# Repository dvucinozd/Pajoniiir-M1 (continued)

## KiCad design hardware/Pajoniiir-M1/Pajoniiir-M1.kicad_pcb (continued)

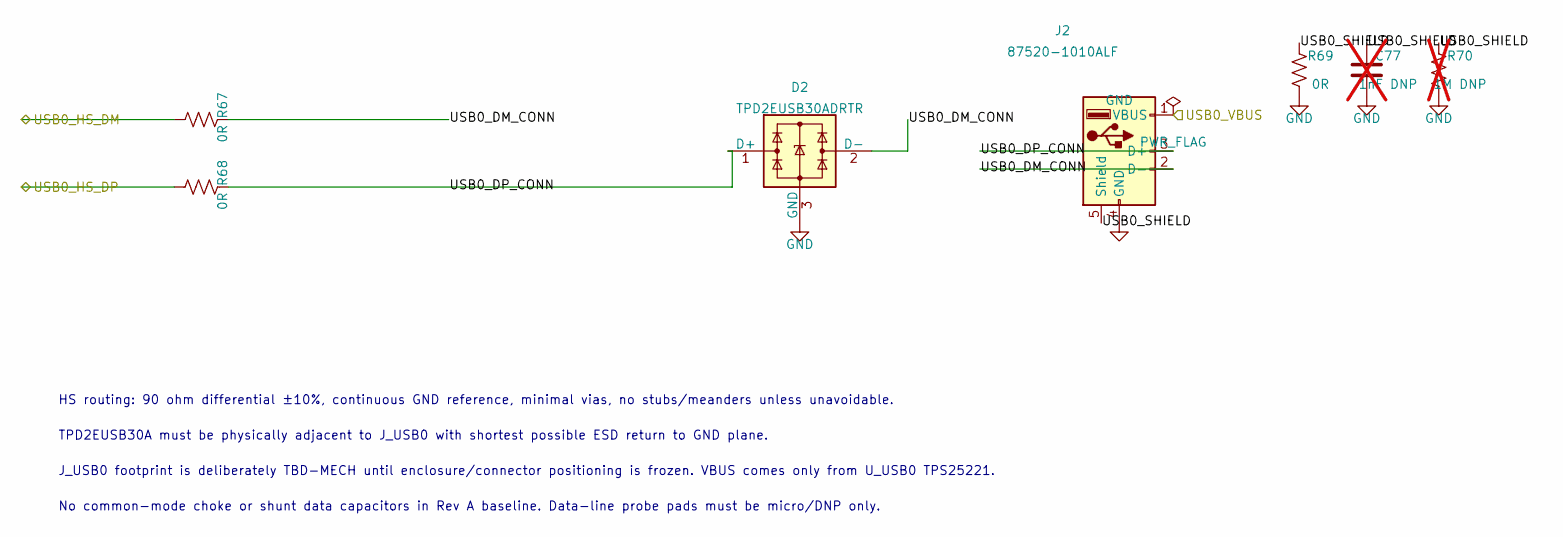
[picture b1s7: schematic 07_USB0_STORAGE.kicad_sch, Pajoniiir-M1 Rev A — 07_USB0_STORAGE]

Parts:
C77: 1nF DNP; C_0603_1608Metric; not fitted
D2: TPD2EUSB30ADRTR; Texas_DRT-3
J2: 87520-1010ALF; Amphenol_87520-1010ALF
R67, R68: 0R; R_0402_1005Metric
R69: 0R; R_0603_1608Metric
R70: 1M DNP; R_0603_1608Metric; not fitted

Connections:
/07_USB0_STORAGE/USB0_DM_CONN: D2.2 (D-), J2.2 (D-), R67.2
/07_USB0_STORAGE/USB0_DP_CONN: D2.1 (D+), J2.3 (D+), R68.2
/07_USB0_STORAGE/USB0_SHIELD: C77.1, J2.5 (Shield), R69.1, R70.1
/USB0_HS_DM: R67.1; also elsewhere on the board
/USB0_HS_DP: R68.1; also elsewhere on the board
/USB0_VBUS: J2.1 (VBUS); also elsewhere on the board

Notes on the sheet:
HS routing: 90 ohm differential ±10%, continuous GND reference, minimal vias, no stubs/meanders unless unavoidable.
TPD2EUSB30A must be physically adjacent to J_USB0 with shortest possible ESD return to GND plane.
J_USB0 footprint is deliberately TBD-MECH until enclosure/connector positioning is frozen. VBUS comes only from U_USB0 TPS25221.
No common-mode choke or shunt data capacitors in Rev A baseline. Data-line probe pads must be micro/DNP only.

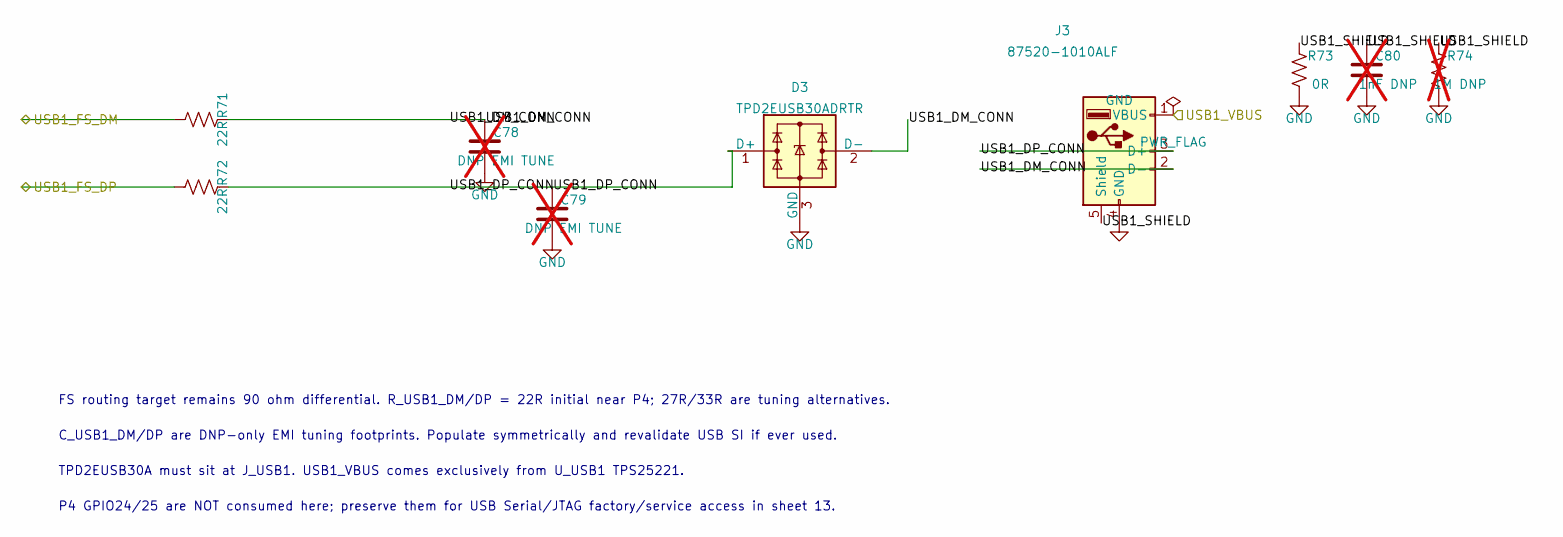
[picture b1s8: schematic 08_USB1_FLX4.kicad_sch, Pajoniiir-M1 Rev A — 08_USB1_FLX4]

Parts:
C78, C79: DNP EMI TUNE; C_0402_1005Metric; not fitted
C80: 1nF DNP; C_0603_1608Metric; not fitted
D3: TPD2EUSB30ADRTR; Texas_DRT-3
J3: 87520-1010ALF; Amphenol_87520-1010ALF
R71, R72: 22R; R_0402_1005Metric
R73: 0R; R_0603_1608Metric
R74: 1M DNP; R_0603_1608Metric; not fitted

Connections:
/08_USB1_FLX4/USB1_DM_CONN: C78.1, D3.2 (D-), J3.2 (D-), R71.2
/08_USB1_FLX4/USB1_DP_CONN: C79.1, D3.1 (D+), J3.3 (D+), R72.2
/08_USB1_FLX4/USB1_SHIELD: C80.1, J3.5 (Shield), R73.1, R74.1
/USB1_FS_DM: R71.1; also elsewhere on the board
/USB1_FS_DP: R72.1; also elsewhere on the board
/USB1_VBUS: J3.1 (VBUS); also elsewhere on the board

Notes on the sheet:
FS routing target remains 90 ohm differential. R_USB1_DM/DP = 22R initial near P4; 27R/33R are tuning alternatives.
C_USB1_DM/DP are DNP-only EMI tuning footprints. Populate symmetrically and revalidate USB SI if ever used.
TPD2EUSB30A must sit at J_USB1. USB1_VBUS comes exclusively from U_USB1 TPS25221.
P4 GPIO24/25 are NOT consumed here; preserve them for USB Serial/JTAG factory/service access in sheet 13.

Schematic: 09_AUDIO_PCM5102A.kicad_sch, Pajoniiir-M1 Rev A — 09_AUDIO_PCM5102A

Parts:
C81, C83, C85, C87: 10uF; C_0805_2012Metric
C82, C84, C86, C90: 100nF; C_0603_1608Metric
C88, C89: 2.2uF; C_0603_1608Metric
C91, C92: 2.2nF C0G; C_0603_1608Metric
J4: KLPX-0848A-2-W-G; Kycon_KLPX-0848A-2-x-G
J5: KLPX-0848A-2-R-G; Kycon_KLPX-0848A-2-x-G
R75, R76, R77: 22R; R_0402_1005Metric
R78: 100R; R_0603_1608Metric
R79: 100k; R_0603_1608Metric
R80, R81: 470R; R_0603_1608Metric
U5: PCM5102APWR; TSSOP-20_4.4x6.5mm_P0.65mm

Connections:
/3V3_AUDIO: C81.1, C82.1, C83.1, C84.1, C85.1, C86.1, C87.1, U5.1 (CPVDD), U5.8 (AVDD), U5.20 (DVDD); also elsewhere on the board
/09_AUDIO_PCM5102A/DAC_CAPM: C88.2, U5.4 (CAPM)
/09_AUDIO_PCM5102A/DAC_CAPP: C88.1, U5.2 (CAPP)
/09_AUDIO_PCM5102A/DAC_DATA_DAC: R76.2, U5.14 (DIN)
/09_AUDIO_PCM5102A/DAC_LDOO_1V8: C90.1, U5.18 (LDOO)
/09_AUDIO_PCM5102A/DAC_VNEG: C89.1, U5.5 (VNEG)
/09_AUDIO_PCM5102A/MAIN_L: C91.1, J4.1 (In), R80.2
/09_AUDIO_PCM5102A/MAIN_R: C92.1, J5.1 (In), R81.2
/DAC_BCLK: R77.1; also elsewhere on the board
/DAC_DATA: R76.1; also elsewhere on the board
/DAC_LRCK: R75.1; also elsewhere on the board
/DAC_XSMT: R78.1; also elsewhere on the board
unnamed: R77.2, U5.13 (BCK)
unnamed: R75.2, U5.15 (LRCK)
unnamed: R80.1, U5.6 (OUTL)
unnamed: R81.1, U5.7 (OUTR)
unnamed: R78.2, R79.1, U5.17 (XSMT)

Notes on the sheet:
PCM5102A 3-wire mode: SCK=GND; FMT=LOW (I2S); FLT=LOW; DEMP=LOW. No external MCLK is required.
XSMT defaults LOW via 100k pulldown. Firmware starts stable BCLK/LRCK/DATA, waits, then drives DAC_XSMT HIGH.
Single 3V3_AUDIO supply for CPVDD/DVDD/AVDD. LDOO is an internal ~1.8V output and is decoupled only.
MAIN_L/R are ground-centered DirectPath line outputs: 470R + 2.2nF, no series DC-block capacitors.
RCA J4/J5 Kycon KLPX-0848A gold-family footprints are locked; final panel XY/cutouts remain open. J6 / 3.5mm line-out was removed from Rev A in M1-MECH-A8; CUE/headphones remain via FLX4 USB Audio.

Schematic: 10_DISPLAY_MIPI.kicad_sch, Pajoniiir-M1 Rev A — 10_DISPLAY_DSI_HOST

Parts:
C93: 100nF; C_0603_1608Metric
C94: 10uF; C_0805_2012Metric
FB3: 0R / ferrite option; R_0603_1608Metric
J6: 15-pin Raspberry-Pi-style DSI host; Amphenol_SFW15R-2STE1LF
R82, R83, R84, R85, R86, R87: 0R; R_0201_0603Metric
R95, R96: 22R; R_0402_1005Metric
R97, R98: 4.7k; R_0603_1608Metric
R99, R100: 4.7k DNP; R_0603_1608Metric; not fitted
TP1: 3V3_DISPLAY_MODULE; TestPoint_Pad_D1.5mm
TP2: P4_LDO_MIPI_2V5; TestPoint_Pad_D1.5mm
TP9: J6_I2C_SDA; TestPoint_Pad_D1.5mm
TP10: J6_I2C_SCL; TestPoint_Pad_D1.5mm

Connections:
/3V3_SYS: FB3.1; also elsewhere on the board
/10_DISPLAY_MIPI/3V3_DISPLAY_MODULE: C93.1, C94.1, FB3.2, J6.14 (3V3), J6.15 (3V3), R97.1, R98.1, R99.1, R100.1, TP1.1
/10_DISPLAY_MIPI/J6_DSI_CLK_N: J6.5 (DSI_CLK_N), R87.2
/10_DISPLAY_MIPI/J6_DSI_CLK_P: J6.6 (DSI_CLK_P), R86.2
/10_DISPLAY_MIPI/J6_DSI_D0_N: J6.8 (DSI_D0_N), R83.2
/10_DISPLAY_MIPI/J6_DSI_D0_P: J6.9 (DSI_D0_P), R82.2
/10_DISPLAY_MIPI/J6_DSI_D1_N: J6.2 (DSI_D1_N), R85.2
/10_DISPLAY_MIPI/J6_DSI_D1_P: J6.3 (DSI_D1_P), R84.2
/10_DISPLAY_MIPI/J6_I2C_SCL: J6.11 (I2C_SCL), R96.2, R98.2, R100.2, TP10.1
/10_DISPLAY_MIPI/J6_I2C_SDA: J6.12 (I2C_SDA), R95.2, R97.2, R99.2, TP9.1
/DISPLAY_I2C_SCL: R96.1; also elsewhere on the board
/DISPLAY_I2C_SDA: R95.1; also elsewhere on the board
/DSI_CLK_N: R87.1; also elsewhere on the board
/DSI_CLK_P: R86.1; also elsewhere on the board
/DSI_D0_N: R83.1; also elsewhere on the board
/DSI_D0_P: R82.1; also elsewhere on the board
/DSI_D1_N: R85.1; also elsewhere on the board
/DSI_D1_P: R84.1; also elsewhere on the board
/P4_LDO_MIPI_2V5: TP2.1; also elsewhere on the board

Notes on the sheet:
DISPLAY INTERFACE: generic 15-pin Raspberry-Pi-style DSI host. DSI506/DYL0023 is one validated profile.
J6 = Amphenol SFW15R-2STE1LF, 15P 1.0mm TOP contact. Locked host map: GND/D1/CLK/D0/I2C/3V3.
DSI506 PROFILE: panel power/backlight 0x45; touch 0x38 at 100kHz. Other displays require a qualified profile.
DSI506 PROFILE: 1 lane @ 800Mbps, RGB888, 27.777MHz, H 59/2/45, V 109/2/22; both physical lanes are routed.
DSI routing target 100R differential; MIPI DPHY 2.5V LDO and 4.02k DSI_REXT remain in 03_P4_CORE.

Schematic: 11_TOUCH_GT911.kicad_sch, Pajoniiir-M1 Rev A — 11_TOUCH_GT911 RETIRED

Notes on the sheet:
M1-ELEC-B2/B7: separate GT911 hardware retired. Touch is supplied by the selected DSI display profile over shared I2C; DSI506 uses 0x38.
GPIO7/8 I2C conditioning, pull-ups and test points moved into 10_DISPLAY_MIPI next to final J8 connector.
GPIO3 TOUCH_RST and GPIO4 TOUCH_INT are released/NC in final M1 architecture.

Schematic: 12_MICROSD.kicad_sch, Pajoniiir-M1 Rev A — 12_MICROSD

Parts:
C101, C104: 100nF; C_0603_1608Metric
C102: 1uF; C_0603_1608Metric
C103: 470pF >=25V; C_0402_1005Metric
C105: 10uF; C_0805_2012Metric
C106: 22uF DNP; C_1206_3216Metric; not fitted
C107: DNP SI TUNE; C_0402_1005Metric; not fitted
J7: 503398-1892; Molex_503398-1892
R104: 100k; R_0603_1608Metric
R105: 100R; R_0603_1608Metric
R106, R107, R108, R110, R111: 0R; R_0402_1005Metric
R109: 22R; R_0402_1005Metric
R112, R113, R114, R115, R116, R117: 10k; R_0603_1608Metric
U13: TPS22918DBVR; SOT-23-6

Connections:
/3V3_SYS: C101.1, C102.1, R117.1, U13.1 (VIN); also elsewhere on the board
/12_MICROSD/3V3_SD: C104.1, C105.1, C106.1, J7.4 (VDD), R105.2, R112.1, R113.1, R114.1, R115.1, R116.1, U13.6 (VOUT)
/12_MICROSD/SD_CLK_CARD: C107.1, J7.5 (CLK), R109.2
/12_MICROSD/SD_CMD_CARD: J7.3 (CMD), R108.2, R114.2
/12_MICROSD/SD_D0_CARD: J7.7 (DAT0), R110.2, R115.2
/12_MICROSD/SD_D1_CARD: J7.8 (DAT1), R111.2, R116.2
/12_MICROSD/SD_D2_CARD: J7.1 (DAT2), R106.2, R112.2
/12_MICROSD/SD_D3_CARD: J7.2 (DAT3/CD), R107.2, R113.2
/SDMMC_CLK: R109.1; also elsewhere on the board
/SDMMC_CMD: R108.1; also elsewhere on the board
/SDMMC_D0: R110.1; also elsewhere on the board
/SDMMC_D1: R111.1; also elsewhere on the board
/SDMMC_D2: R106.1; also elsewhere on the board
/SDMMC_D3: R107.1; also elsewhere on the board
/SD_CARD_DETECT: J7.9 (DET), R117.2; also elsewhere on the board
/SD_PWR_EN: R104.2, U13.3 (ON); also elsewhere on the board
unnamed: C103.1, U13.4 (CT)
unnamed: R105.1, U13.5 (QOD)

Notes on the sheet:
SDMMC0 fixed IO-MUX: GPIO39 D0, GPIO40 D1, GPIO41 D2, GPIO42 D3, GPIO43 CLK, GPIO44 CMD.
TPS22918: SD rail defaults OFF. CT=470pF initial; QOD=100R initial; 3V3_SD must fully discharge for true card reset.
CMD/D0..D3 pull-ups are 10k to switched 3V3_SD. CLK has no pull-up; CLK series=22R and a DNP shunt-C tuning footprint.
Before SD power-off firmware must stop SDMMC and make GPIO39-44 high-Z to prevent back-power through card I/O protection.
J_SD footprint and low-cap multi-line ESD array remain TBD. Socket shield is direct GND; card-detect is active-low when supported.

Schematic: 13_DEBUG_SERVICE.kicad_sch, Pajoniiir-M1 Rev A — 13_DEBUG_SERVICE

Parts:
C108, C109: DNP EMI TUNE; C_0402_1005Metric; not fitted
J8: P4 DEBUG TC2030-NL DNL; Tag-Connect_TC2030-IDC-NL_2x03_P1.27mm_Vertical; not fitted
J9: P4 USB SERIAL/JTAG FACTORY POGO DNL; Factory_Pogo_USBJTAG_1x05_P1.27_2Tooling; not fitted
J10: C6 DEBUG TC2030-NL DNL; Tag-Connect_TC2030-IDC-NL_2x03_P1.27mm_Vertical; not fitted
R118, R119: 22R; R_0402_1005Metric
TP13: BOOT_GPIO36; TestPoint_Pad_D1.5mm
TP14: C6_BOOT_GPIO8; TestPoint_Pad_D1.5mm
TP15: DEBUG_UART_TX; TestPoint_Pad_D1.5mm
TP16: DEBUG_UART_RX; TestPoint_Pad_D1.5mm
TP17: CHIP_PU; TestPoint_Pad_D1.5mm
TP18: USBJTAG_DM_SERVICE; TestPoint_Pad_D1.5mm
TP19: USBJTAG_DP_SERVICE; TestPoint_Pad_D1.5mm
TP20: C6_EN; TestPoint_Pad_D1.5mm

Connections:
/3V3_C6: J10.5; also elsewhere on the board
/3V3_SYS: J8.5, J9.5; also elsewhere on the board
/13_DEBUG_SERVICE/USBJTAG_DM_SERVICE: C108.1, J9.3, R118.2, TP18.1
/13_DEBUG_SERVICE/USBJTAG_DP_SERVICE: C109.1, J9.2, R119.2, TP19.1
/BOOT_GPIO35: J8.2; also elsewhere on the board
/BOOT_GPIO36: TP13.1; also elsewhere on the board
/C6_BOOT_GPIO8: TP14.1; also elsewhere on the board
/C6_BOOT_GPIO9: J10.2; also elsewhere on the board
/C6_EN: J10.4, TP20.1; also elsewhere on the board
/C6_UART_RX: J10.3; also elsewhere on the board
/C6_UART_TX: J10.6; also elsewhere on the board
/CHIP_PU: J8.4, J9.1, TP17.1; also elsewhere on the board
/DEBUG_UART_RX: J8.3, TP16.1; also elsewhere on the board
/DEBUG_UART_TX: J8.6, TP15.1; also elsewhere on the board
/P4_USBJTAG_DM: R118.1; also elsewhere on the board
/P4_USBJTAG_DP: R119.1; also elsewhere on the board

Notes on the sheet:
JDBG_P4 and JDBG_C6 are no-parts Tag-Connect footprints (DNL). Pin-1 VREF is sense/reference only, never a board power input.
P4 UART conditioning is already in sheet 04; C6 UART conditioning is already in sheet 05. Do not duplicate those series resistors here.
P4 USB Serial/JTAG uses GPIO24/25 through 22R/22R. DNP shunt capacitors are symmetrical tuning-only footprints.
Factory recovery is independent of display/Wi-Fi/application firmware: P4 UART0, P4 USB Serial/JTAG and C6 UART/boot all remain accessible.

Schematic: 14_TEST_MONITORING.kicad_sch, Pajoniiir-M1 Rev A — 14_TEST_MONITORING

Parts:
C110, C111: 100nF; C_0603_1608Metric
C112: 1uF; C_0603_1608Metric
R120: WSK25125L000FEA / 5mR 1% 1W; R_Shunt_Vishay_WSK2512_6332Metric_T1.19mm
R121, R122: 10R; R_0603_1608Metric
R123: 10k; R_0603_1608Metric
TP21: 5V_PROTECTED; TestPoint_Pad_D1.5mm
TP22: 5V_SYS; TestPoint_Pad_D1.5mm
TP23: 3V3_SYS; TestPoint_Pad_D1.5mm
TP24: SYS_POWER_ALERT_N; TestPoint_Pad_D1.5mm
U14: INA238AIDGSR; Texas_DGS0010A_VSSOP-10_3x3mm_P0.5mm

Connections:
/3V3_SYS: C111.1, C112.1, R123.1, TP23.1, U14.6 (VS); also elsewhere on the board
/5V_PROTECTED: R120.1, R121.1, TP21.1; also elsewhere on the board
/5V_SYS: R120.2, R122.1, TP22.1, U14.8 (Vbus); also elsewhere on the board
/14_TEST_MONITORING/INA_INN_FILT: C110.2, R122.2, U14.9 (Vin-)
/14_TEST_MONITORING/INA_INP_FILT: C110.1, R121.2, U14.10 (Vin+)
/DISPLAY_I2C_SCL: U14.5 (SCL); also elsewhere on the board
/DISPLAY_I2C_SDA: U14.4 (SDA); also elsewhere on the board
/SYS_POWER_ALERT_N: R123.2, TP24.1, U14.3 (~Alert); also elsewhere on the board

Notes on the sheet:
R_SYS_SHUNT = WSK25125L000FEA, 5mR 1% 1W, 4-terminal/Kelvin. At 4.5A: 22.5mV, ~101mW.
INA238 address 0x40: A0=A1=GND. VBUS senses load-side 5V_SYS; IN+ = supply-side Kelvin, IN- = load-side Kelvin.
Input filter: 10R + 10R and 100nF differential. Do not route sense traces on shared high-current copper; take Kelvin taps at shunt pads.
Cost-down: U_MON/filter/ALERT may be DNP, but R_SYS_SHUNT must remain or be replaced by footprint-compatible 0R high-current jumper.
Shared I2C uses existing bus pull-ups; do not add another strong pull-up pair on this sheet.

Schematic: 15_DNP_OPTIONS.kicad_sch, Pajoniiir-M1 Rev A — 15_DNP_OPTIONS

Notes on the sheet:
ASSEMBLY POLICY
Functional DNP/tuning footprints live on their owning sheets. This sheet is control documentation only.
POWER
01: input bulk alternatives = DNP tuning; 02: FB_C6 / FB_AUDIO are 0R defaults with ferrite option; 10: FB_LCD; 11: FB_TOUCH.
14: INA238 is POP for EVT/DVT and may become DNP in production. R_SYS_SHUNT must remain populated or be replaced by approved footprint-compatible 0R jumper.
USB0 HIGH-SPEED
R_USB0_DM/DP = 0R POP tuning. C_USB0_OUT_OPT = 100uF DNP. Shield 1nF + 1M options DNP. No CMC in Rev A baseline.
USB1 FULL-SPEED
R_USB1_DM/DP = 22R POP initial. C_USB1_DM/DP = DNP EMI tuning. C_USB1_OUT_OPT = 100uF DNP. Shield 1nF + 1M options DNP.
FLASH / CLOCK
QSPI series 0R tuning footprints POP. Crystal load values are assembly-selection values, not simultaneously populated alternatives.
AUDIO
J_LINE_35 = DNP optional line-level output. No headphone amp, speaker amp, ES8311, microphone or legacy monitor-I2S DNP footprints.
DISPLAY / TOUCH
10: DSI six inline 0R = POP. R_LCD_TE_SER = DNP. No external MIPI ESD baseline. Physical J_LCD footprint remains BLOCKED, not DNP.
11: R_TOUCH_SDA_PU2 / R_TOUCH_SCL_PU2 = DNP pull-up tuning. Optional touch ESD remains uninstantiated until enclosure exposure requires it.
MICROSD
C_SD_OUT_OPT = 22uF DNP. C_SD_CLK_TUNE = DNP SI tuning. Optional low-C SD ESD waits for final socket/layout. TPS22918 is mandatory POP.
DEBUG / FACTORY
JDBG_P4 and JDBG_C6 = DNL Tag-Connect PCB pads. JDBG_USB = DNL pogo footprint. C_P4_USBJTAG_DM/DP = DNP tuning.
PROHIBITED LEGACY FOOTPRINTS
NO ESP32-S3
NO ES8311
NO speaker amplifier / speaker connector
NO analog microphone
NO MAX485 / RS485
NO MIPI CSI camera block
NO P4<->S3 legacy UART bridge
NO legacy monitor I2S bridge
NO battery charger / IP5306 baseline
NO generic large expansion header
VARIANT INTENT
EVT: populate INA238; expose all tuning/test infrastructure; debug fixtures remain DNL pads.
DVT: retain telemetry and selected tuning values; validate EMI/SI/thermal margins and decide cost-down.
PROD: only validated tuning values; optional telemetry decision after DVT; no open main power path allowed.
HARD GATES BEFORE PCB FREEZE
1. Authoritative LCD panel MPN + FPC pin order + pitch/contact-side + 30-vs-32 resolution.
2. Exact USB-A mechanical connector MPNs / board-edge placement.
3. Exact microSD socket MPN / card-detect mechanics.
4. RCA / optional 3.5mm mechanical MPNs and enclosure datum.

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
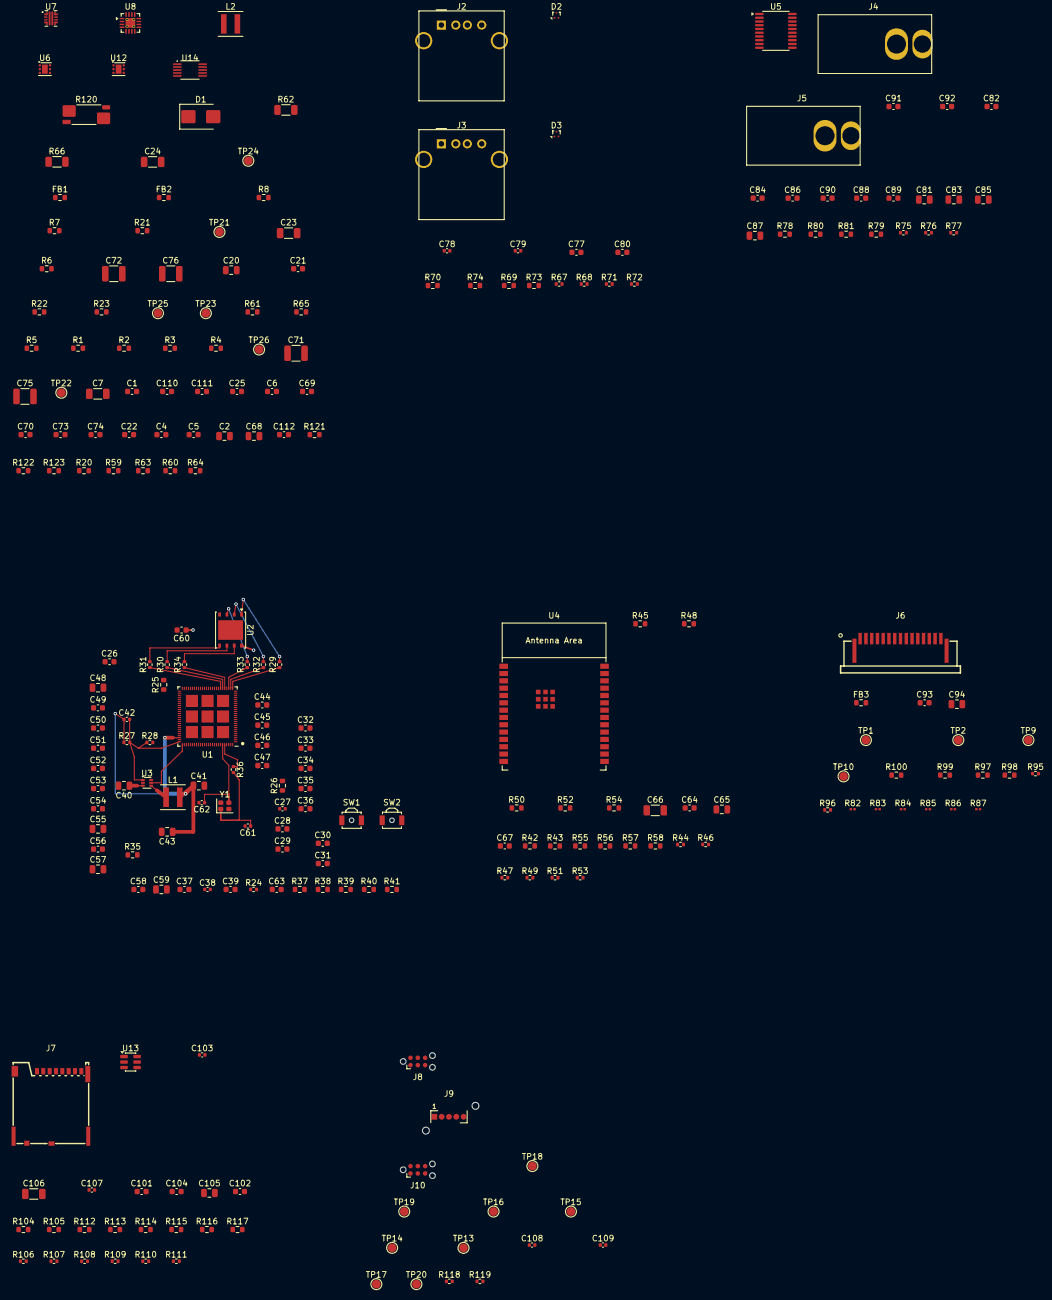
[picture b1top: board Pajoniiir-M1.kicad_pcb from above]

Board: 4 copper layers, 244 parts (0 on the bottom side), 149 nets.

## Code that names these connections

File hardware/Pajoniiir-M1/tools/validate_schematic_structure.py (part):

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                )

            expected_unit2 = {
                "DISPLAY_I2C_SDA": "GPIO7",
                "DISPLAY_I2C_SCL": "GPIO8",
                "C6_SDIO_D0": "GPIO14",
                "C6_SDIO_D1": "GPIO15",
                "C6_SDIO_D2": "GPIO16/ADC1_CHANNEL0",
                "C6_SDIO_D3": "GPIO17/ADC1_CHANNEL1",
                "C6_SDIO_CLK": "GPIO18/ADC1_CHANNEL2",
                "C6_SDIO_CMD": "GPIO19/ADC1_CHANNEL3",
                "USB0_PWR_EN": "GPIO20/ADC1_CHANNEL4",
                "USB0_FAULT_N": "GPIO21/ADC1_CHANNEL5",
                "USB1_PWR_EN": "GPIO22/ADC1_CHANNEL6",
                "FLASH_CS": "FLASH_CS",
                "FLASH_Q": "FLASH_Q",
                "FLASH_WP": "FLASH_WP",
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                "DSI_D0_N": "DSI_DATAN0",
                "USB0_HS_DM": "USB-DM",
                "USB0_HS_DP": "USB-DP",
                "P4_USBJTAG_DM": "GPIO24/USB1P1_N0",
                "P4_USBJTAG_DP": "GPIO25/USB1P1_P0",
                "USB1_FS_DM": "GPIO26/USB1P1_N1",
                "USB1_FS_DP": "GPIO27/USB1P1_P1",
                "USB1_FAULT_N": "GPIO32",
                "BOOT_GPIO35": "GPIO35",
                "BOOT_GPIO36": "GPIO36",
                "UART0_TX": "GPIO37",
                "UART0_RX": "GPIO38",
                "SDMMC_D0": "GPIO39",
                "SDMMC_D1": "GPIO40",
                "SDMMC_D2": "GPIO41",
                "SDMMC_D3": "GPIO42",
                "SDMMC_CLK": "GPIO43",
                "SDMMC_CMD": "GPIO44",
                "SD_PWR_EN": "GPIO45",
                "SD_CARD_DETECT": "GPIO46",
                "DAC_XSMT": "GPIO49/ADC2_CHANNEL0",
                "DAC_BCLK": "GPIO50/ADC2_CHANNEL1",
                "DAC_DATA": "GPIO51/ADC2_CHANNEL2",
                "DAC_LRCK": "GPIO52/ADC2_CHANNEL3",
                "SYS_POWER_ALERT_N": "GPIO53/ADC2_CHANNEL4",
                "C6_RESET": "GPIO54/ADC2_CHANNEL5",
            }

            def close_xy(
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                unused_unit2 = {
                    "GPIO0", "GPIO1", "GPIO2",
                    "GPIO3", "GPIO4", "GPIO5", "GPIO6",
                    "GPIO9", "GPIO10", "GPIO11", "GPIO12", "GPIO13",
                    "GPIO23/ADC1_CHANNEL7",
                    "CSI_DATAN0", "CSI_DATAP0", "CSI_CLKP", "CSI_CLKN",
                    "CSI_DATAN1", "CSI_DATAP1", "CSI_REXT",
                    "GPIO28", "GPIO29", "GPIO30", "GPIO31",
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                            f"03_P4_CORE: unused U1/2 {pin_name} lacks explicit NC"
                        )

                dsi_rext = unit2_pins.get("DSI_REXT")
                if dsi_rext:
                    dsi_target = (ux + dsi_rext[1], uy - dsi_rext[2])
                    xy_points = [
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                    ]
                    if not any(close_xy(point, dsi_target) for point in xy_points):
                        errors.append(
                            "03_P4_CORE: DSI_REXT physical pin is not wired"
                        )
                if "R24" not in p03 or "4.02k 1%" not in p03:
                    errors.append(
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
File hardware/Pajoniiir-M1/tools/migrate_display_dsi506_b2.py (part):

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
    body.append(hier("P4_LDO_MIPI_2V5", "input", 30, 40, "h-mipi25"))
    body.append(tp("TP2", "P4_LDO_MIPI_2V5", 120, 40, "TP2"))
    body.append(label("P4_LDO_MIPI_2V5", 120, 40, "l-tp2"))

    dsi = [
        ("DSI_D0_P", "R82", "J6_DSI_D0_P", 50),
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        body.append(label("3V3_DISPLAY_MODULE", x, y - 3.81, "l-" + ref + "-v"))
        body.append(label(out, x, y + 3.81, "l-" + ref + "-bus"))
    body.append(tp("TP9", "J6_I2C_SDA", 135, 108, "TP9"))
    body.append(label("J6_I2C_SDA", 135, 108, "l-tp9"))
    body.append(tp("TP10", "J6_I2C_SCL", 145, 118, "TP10"))
    body.append(label("J6_I2C_SCL", 145, 118, "l-tp10"))

    body.append(
        inst(
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    )
    stub = f'''
  (text "M1-ELEC-B2: separate GT911 support retired. Final DSI506/DYL0023 touch is module-integrated at I2C 0x38." (exclude_from_sim no) (at 35 55 0) (effects (font (size 1.27 1.27)) (justify left)) (uuid "{U('stub1')}"))
  (text "GPIO7/8 I2C conditioning, pull-ups and test points moved into 10_DISPLAY_MIPI next to final J6 connector." (exclude_from_sim no) (at 35 60 0) (effects (font (size 1.27 1.27)) (justify left)) (uuid "{U('stub2')}"))
  (text "GPIO3 TOUCH_RST and GPIO4 TOUCH_INT are released/NC in final M1 architecture." (exclude_from_sim no) (at 35 65 0) (effects (font (size 1.27 1.27)) (justify left)) (uuid "{U('stub3')}"))
  (sheet_instances (path "/" (page "12")))
  (embedded_fonts no)
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
def migrate_p4() -> None:
    text = P03.read_text()
    if 'hierarchical_label "DISPLAY_I2C_SDA"' in text and 'hierarchical_label "TOUCH_RST"' not in text:
        print("P4 already migrated")
        return
    text = text.replace('"I2C_SDA"', '"DISPLAY_I2C_SDA"').replace('"I2C_SCL"', '"DISPLAY_I2C_SCL"')
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
def migrate_root() -> None:
    root = ROOT.read_text()
    if '(pin "DISPLAY_I2C_SDA"' in root and '(pin "TOUCH_RST"' not in root and '(pin "LCD_BL_PWM"' not in root:
        print("root already migrated")
        return
    root = root.replace('"I2C_SDA"', '"DISPLAY_I2C_SDA"').replace('"I2C_SCL"', '"DISPLAY_I2C_SCL"')
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    d10s, d10e, d10b = sheets["10_DISPLAY_MIPI"]
    prune_coords.update((x, y) for _, x, y in pin_coords(d10b, {"5V_SYS", "3V3_LCD", "LCD_BL_PWM"}))
    d10b = re.sub(r'\n    \(pin "(?:5V_SYS|3V3_LCD|LCD_BL_PWM)"[^\n]+\)', "", d10b)
    d10b = d10b.replace('(pin "LCD_RST" input', '(pin "DISPLAY_I2C_SDA" bidirectional')
    d10b = d10b.replace('(pin "LCD_TE" bidirectional', '(pin "DISPLAY_I2C_SCL" bidirectional')

    t11s, t11e, t11b = sheets["11_TOUCH_GT911"]
    prune_coords.update((x, y) for _, x, y in pin_coords(t11b, None))
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    for start, end in sorted(set(removals), reverse=True):
        root = root[:start] + root[end:]

    root = root.replace('(label "LCD_RST"', '(label "DISPLAY_I2C_SDA"')
    root = root.replace('(label "LCD_TE"', '(label "DISPLAY_I2C_SCL"')
    if balance(root) != (0, 0):
        raise SystemExit(f"root balance {balance(root)}")
    for name in obsolete:
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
